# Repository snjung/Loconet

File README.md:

# Loconet
Alles rund um Modellbahn, Arduino und Loconet

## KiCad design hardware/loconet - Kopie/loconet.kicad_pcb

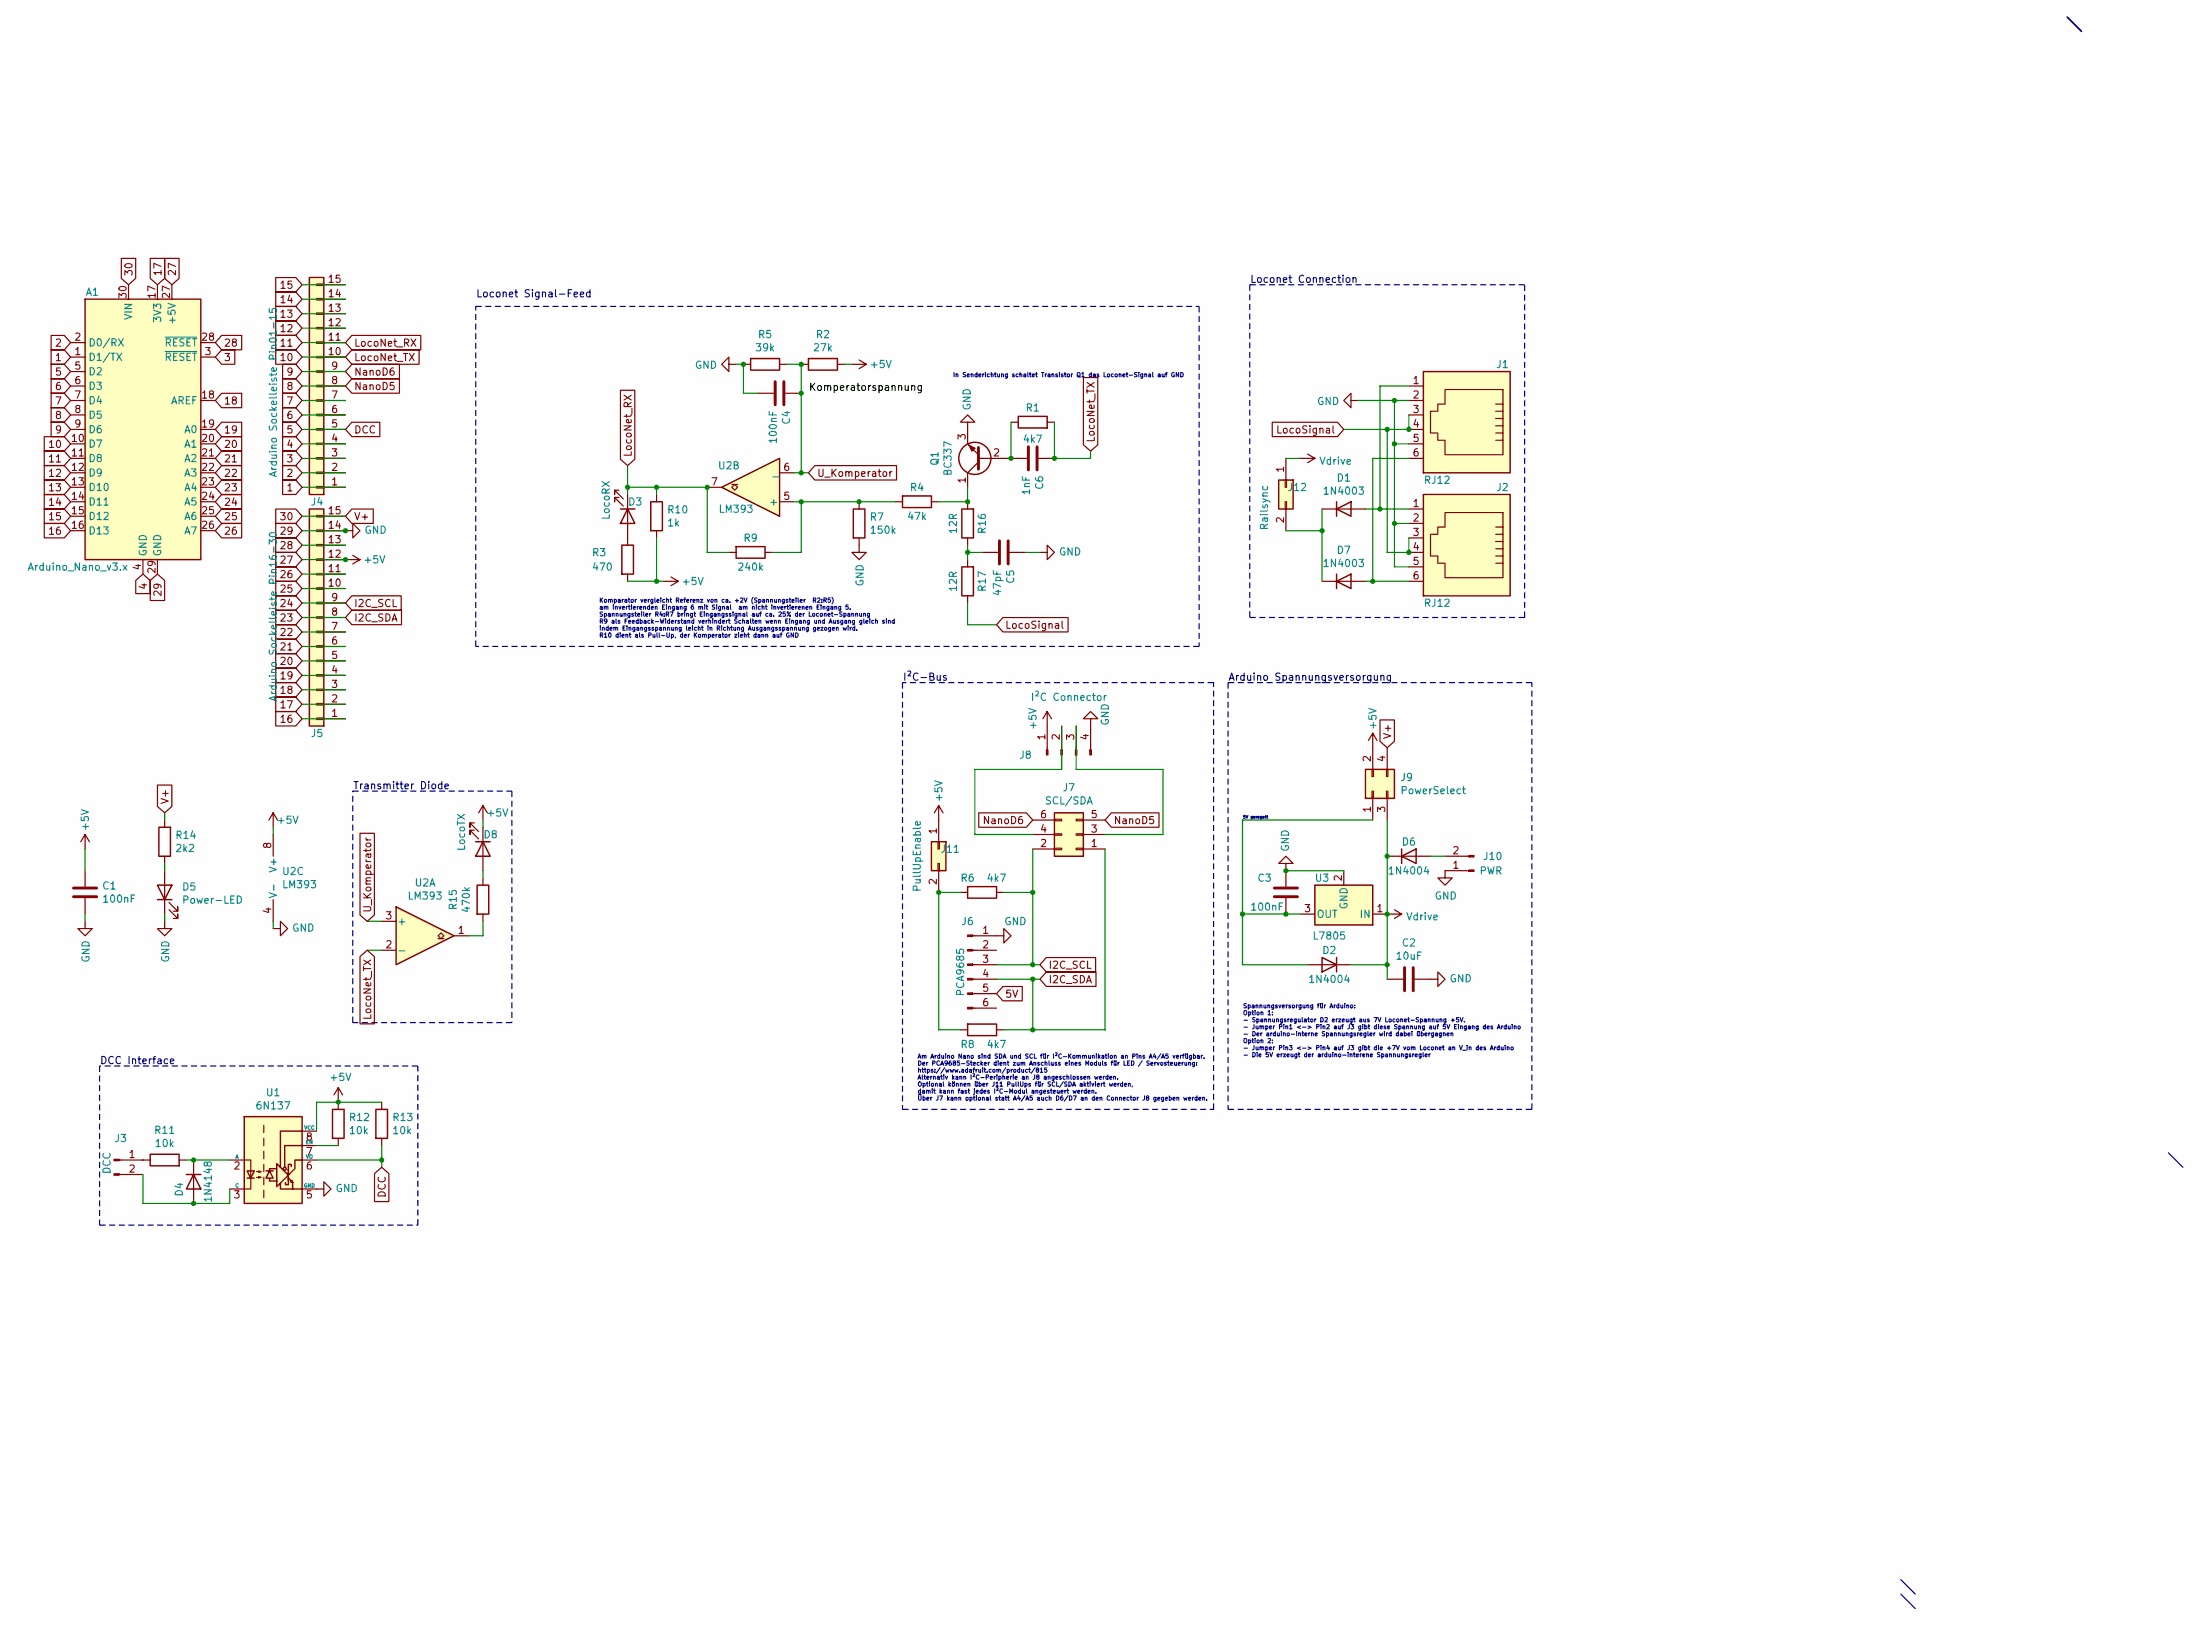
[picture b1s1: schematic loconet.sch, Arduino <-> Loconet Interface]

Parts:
A1: Arduino_Nano_v3.x; Arduino_Nano
C1, C3, C4: 100nF; C_Disc_D4.3mm_W1.9mm_P5.00mm
C2: 10uF; C_Radial_D12.5mm_H20.0mm_P5.00mm
C5: 47pF; C_Disc_D4.3mm_W1.9mm_P5.00mm
C6: 1nF; C_Disc_D4.3mm_W1.9mm_P5.00mm
D1, D7: 1N4003; D_DO-41_SOD81_P10.16mm_Horizontal
D2, D6: 1N4004; D_DO-41_SOD81_P10.16mm_Horizontal
D3: LocoRX; LED_D3.0mm
D4: 1N4148; D_DO-35_SOD27_P7.62mm_Horizontal
D5: Power-LED; LED_D3.0mm
D8: LocoTX; LED_D3.0mm
J1, J2: RJ12; RJ12_Amphenol_54601
J3: DCC; JST_EH_B2B-EH-A_1x02_P2.50mm_Vertical
J4: Arduino Sockelleiste Pin01-15; PinSocket_1x15_P2.54mm_Vertical
J5: Arduino Sockelleiste Pin16-30; PinSocket_1x15_P2.54mm_Vertical
J6: PCA9685; JST_EH_B6B-EH-A_1x06_P2.50mm_Vertical
J7: SCL/SDA; PinHeader_2x03_P2.54mm_Vertical
J8: I²C Connector; JST_EH_B4B-EH-A_1x04_P2.50mm_Vertical
J9: PowerSelect; PinHeader_2x02_P2.54mm_Vertical
J10: PWR; JST_EH_B2B-EH-A_1x02_P2.50mm_Vertical
J11: PullUpEnable; PinHeader_2x01_P2.54mm_Vertical
J12: Railsync; PinHeader_2x01_P2.54mm_Vertical
Q1: BC337; TO-92_Inline
R1, R6, R8: 4k7; R_Axial_DIN0207_L6.3mm_D2.5mm_P7.62mm_Horizontal
R2: 27k; R_Axial_DIN0207_L6.3mm_D2.5mm_P7.62mm_Horizontal
R3: 470; R_Axial_DIN0207_L6.3mm_D2.5mm_P7.62mm_Horizontal
R4: 47k; R_Axial_DIN0207_L6.3mm_D2.5mm_P7.62mm_Horizontal
R5: 39k; R_Axial_DIN0207_L6.3mm_D2.5mm_P7.62mm_Horizontal
R7: 150k; R_Axial_DIN0207_L6.3mm_D2.5mm_P7.62mm_Horizontal
R9: 240k; R_Axial_DIN0207_L6.3mm_D2.5mm_P7.62mm_Horizontal
R10: 1k; R_Axial_DIN0207_L6.3mm_D2.5mm_P7.62mm_Horizontal
R11, R12, R13: 10k; R_Axial_DIN0207_L6.3mm_D2.5mm_P7.62mm_Horizontal
R14: 2k2; R_Axial_DIN0207_L6.3mm_D2.5mm_P7.62mm_Horizontal
R15: 470k; R_Axial_DIN0207_L6.3mm_D2.5mm_P7.62mm_Horizontal
R16, R17: 12R; R_Axial_DIN0207_L6.3mm_D2.5mm_P7.62mm_Horizontal
U1: 6N137; DIP-8_W7.62mm
U2: LM393; DIP-8_W7.62mm_LongPads
U3: L7805; TO-220-3_Vertical

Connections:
1: A1.1 (D1/TX), J4.1
2: A1.2 (D0/RX), J4.2
3: A1.3 (~RESET), J4.3
4: A1.4 (GND), J4.4
5: A1.5 (D2), J4.5, R13.2, U1.6 (VO)
5V: J6.5
6: A1.6 (D3), J4.6
7: A1.7 (D4), J4.7
8: A1.8 (D5), J4.8, J7.5
9: A1.9 (D6), J4.9, J7.6
10: A1.10 (D7), C6.1, J4.10, R1.2, U2.2 (-)
11: A1.11 (D8), D3.1 (K), J4.11, R9.2, R10.1, U2.7
12: A1.12 (D9), J4.12
13: A1.13 (D10), J4.13
14: A1.14 (D11), J4.14
15: A1.15 (D12), J4.15
16: A1.16 (D13), J5.1
17: A1.17 (3V3), J5.2
18: A1.18 (AREF), J5.3
19: A1.19 (A0), J5.4
20: A1.20 (A1), J5.5
21: A1.21 (A2), J5.6
22: A1.22 (A3), J5.7
23: A1.23 (A4), J5.8, J6.4, J7.1, R8.1
24: A1.24 (A5), J5.9, J6.3, J7.2, R6.1
25: A1.25 (A6), J5.10
26: A1.26 (A7), J5.11
27: A1.27 (+5V), C1.1, D8.1 (K), J5.12, J8.1, J9.2, J11.1, R2.1, R3.2, R10.2, R12.1, R13.1, U1.8 (VCC), U2.8 (V+)
28: A1.28 (~RESET), J5.13
29: A1.29 (GND), C1.2, C2.1, C3.1, C4.2, C5.1, D5.1 (K), J1.2, J1.5, J2.2, J2.5, J5.14, J6.1, J8.4, J10.1, Q1.3 (E), R5.2, R7.2, U1.5 (GND), U2.4 (V-), U3.2 (GND)
30: A1.30 (VIN), J5.15, J9.4, R14.2
LocoSignal: J1.3, J1.4, J2.3, J2.4, R17.1
unnamed: C3.2, D2.2 (A), J9.1, U3.3 (OUT)
unnamed: C5.2, R16.1, R17.2
unnamed: C6.2, Q1.2 (B), R1.1
unnamed: D1.1 (K), D7.1 (K), J12.2
unnamed: D1.2 (A), J1.1, J2.1
unnamed: D3.2 (A), R3.1
unnamed: D4.1 (K), R11.2, U1.2 (A)
unnamed: D4.2 (A), J3.2, U1.3 (C)
unnamed: D5.2 (A), R14.1
unnamed: D6.2 (A), J10.2
unnamed: D7.2 (A), J1.6, J2.6
unnamed: D8.2 (A), R15.1
unnamed: J3.1, R11.1
unnamed: J7.3, J8.3
unnamed: J7.4, J8.2
unnamed: J11.2, R6.2, R8.2
unnamed: Q1.1 (C), R4.1, R16.2
unnamed: R4.2, R7.1, R9.1, U2.5 (+)
unnamed: R12.2, U1.7 (EN)
unnamed: R15.2, U2.1
U_Komperator: C4.1, R2.2, R5.1, U2.3 (+), U2.6 (_)
Vdrive: C2.2, D2.1 (K), D6.1 (K), J9.3, J12.1, U3.1 (IN)

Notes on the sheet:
Loconet Connection
Loconet Signal-Feed
DCC Interface
Komparator vergleicht Referenz von ca. +2V (Spannungsteiler R2:R5) am invertierenden Eingang 6 mit Signal am nicht invertierenen Eingang 5. Spannungsteiler R4:R7 bringt Eingangssignal auf ca. 25% der Loconet-Spannung R9 als Feedback-Widerstand verhindert Schalten wenn Eingang und Ausgang gleich sin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
In Senderichtung schaltet Transistor Q1 das Loconet-Signal auf GND
5V geregelt
Spannungsversorgung für Arduino: Option 1: - Spannungsregulator D2 erzeugt aus 7V Loconet-Spannung +5V. - Jumper Pin1 <-> Pin2 auf J3 gibt diese Spannung auf 5V Eingang des Arduino - Der arduino-interne Spannungsregler wird dabei übergagnen Option 2: - Jumper Pin3 <-> Pin4 auf J3 gibt die +7V vom L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
Am Arduino Nano sind SDA und SCL für I²C-Kommunikation an Pins A4/A5 verfügbar. Der PCA9685-Stecker dient zum Anschluss eines Moduls für LED / Servosteuerung: https://www.adafruit.com/product/815 Alternativ kann I²C-Peripherie an J8 angeschlossen werden. Optional können über J11 PullUps für SCL/SDA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
I²C-Bus
Arduino Spannungsversorgung
Transmitter Diode

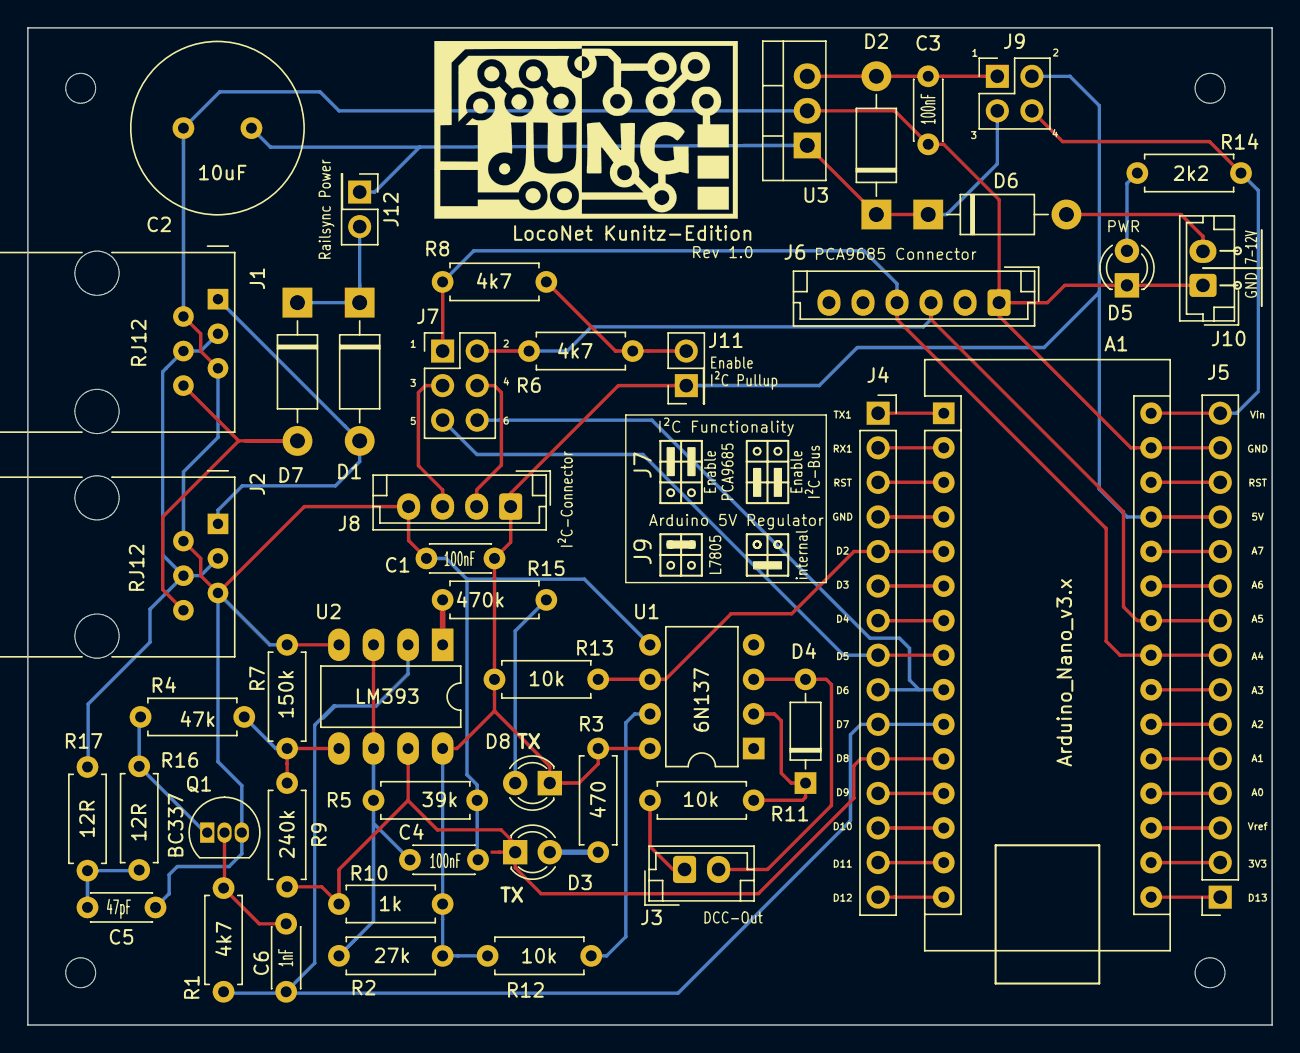
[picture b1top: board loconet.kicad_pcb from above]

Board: 2 copper layers, 91.4 x 73.3 mm, 50 parts (0 on the bottom side), 53 nets.

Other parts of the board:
LOGO**: board-title
LOGO***: LOGO; JungLogo

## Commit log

2020-10-31 Platinendesign für Loconet-Arduino-Schnittstelle erstellt
2020-11-03 Add variant hardware with loconet TX indicator LED
2020-11-03 Einige Verbesserungen am PCB Layout
2020-11-08 Added some capacitors
